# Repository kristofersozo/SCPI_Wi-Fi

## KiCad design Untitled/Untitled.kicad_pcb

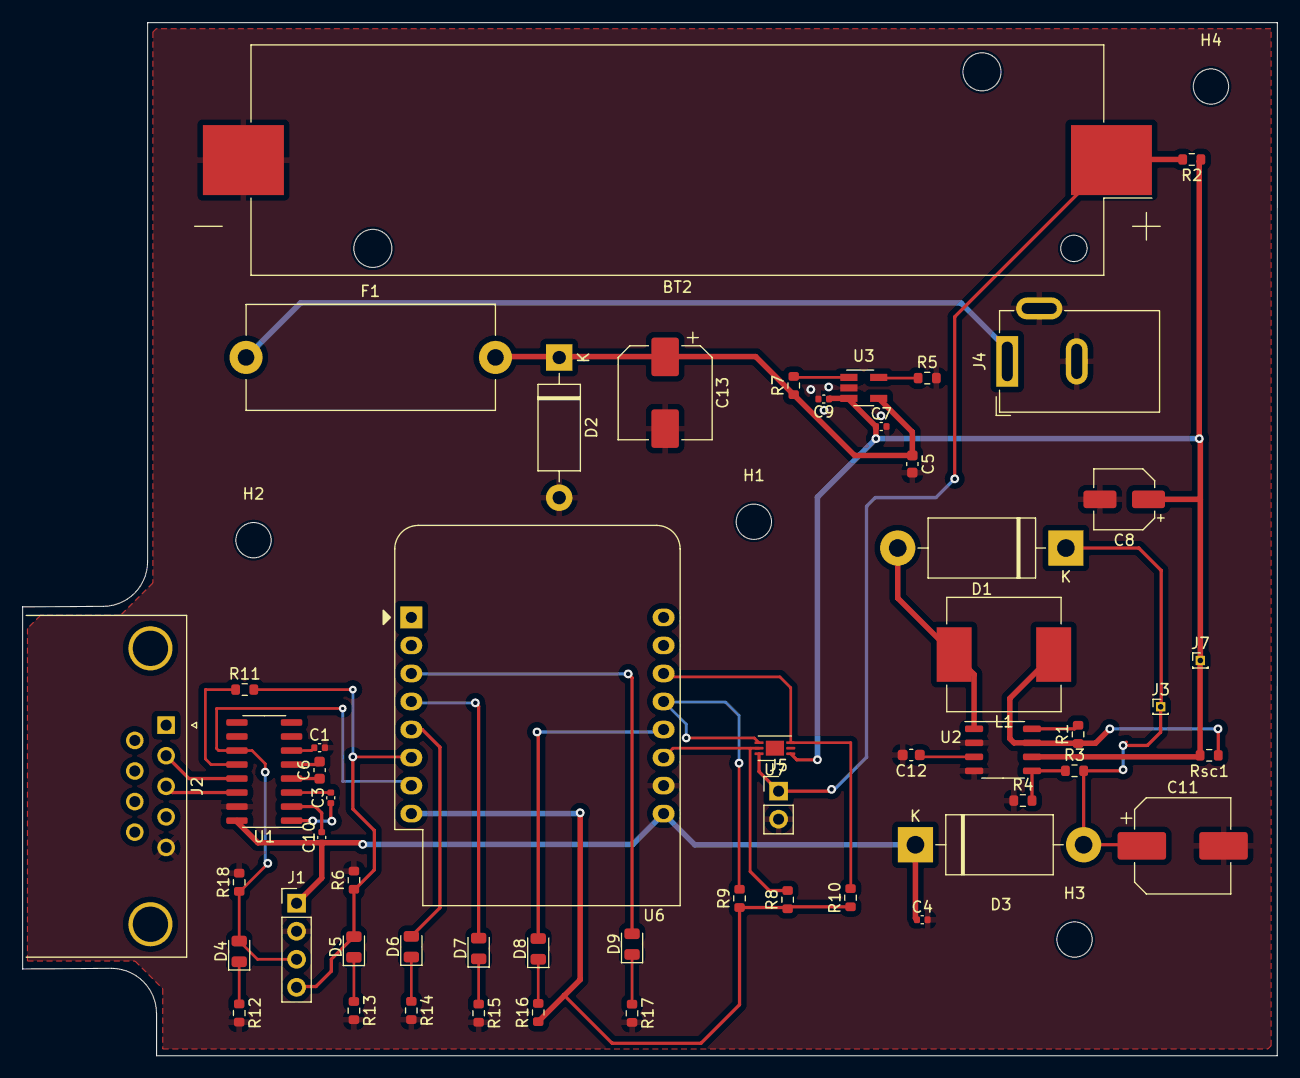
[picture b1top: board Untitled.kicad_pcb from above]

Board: 2 copper layers, 113.7 x 93.6 mm, 58 parts (0 on the bottom side), 39 nets.

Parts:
BT2: Li_ion_Battery_Cell; BatteryHolder_Keystone_1042_1x18650
C1, C3, C4, C7, C9, C10: 100nF; C_0402_1005Metric
C5, C6: 1uF; C_0603_1608Metric
C8: 100uF/16V; CP_Elec_5x5.4
C11: 220uF/16V; CP_Elec_8x10.5
C12: 180pF; C_0603_1608Metric
C13: 4,7uF; CP_Elec_8x10
D1, D3: 1N5822; D_DO-201AD_P15.24mm_Horizontal
D2: SA6.0A; D_DO-15_P12.70mm_Horizontal
D4, D5, D6, D7, D8, D9: LED; LED_0805_2012Metric
F1: 2A; Fuseholder_Cylinder-5x20mm_Stelvio-Kontek_PTF78_Horizontal_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
H1, H2, H3, H4: MountingHole; MountingHole_3.2mm_M3
J1: Conn_01x04_Socket; PinHeader_1x04_P2.54mm_Vertical
J2: DE9_Plug; DSUB-9_Male_Horizontal_P2.77x2.84mm_EdgePinOffset9.90mm_Hou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
J3: 5V5; PinHeader_1x01_P1.00mm_Vertical
J4: Barrel_Jack_Switch_Pin3Ring; BarrelJack_GCT_DCJ200-10-A_Horizontal
J5: Conn_01x02_Pin; PinHeader_1x02_P2.54mm_Vertical
J7: Conn_01x01_Pin; PinHeader_1x01_P1.00mm_Vertical
L1: 7.5uH; L_Vishay_IHLP-4040
R1: 220_1%; R_0603_1608Metric
R2: 100m_1%; R_0603_1608Metric
R3: 47k_1%; R_0603_1608Metric
R4: 15k_1%; R_0603_1608Metric
R5: 1k65_1%; R_0603_1608Metric
R6, R18: 10k_1%; R_0603_1608Metric
R7: 0R_1%; R_0603_1608Metric
R8, R9, R10: 2,2k; R_0603_1608Metric
R11: 5,6K_1%; R_0603_1608Metric
R12, R13, R14, R15, R16, R17: 470_1%; R_0603_1608Metric
Rsc1: 1,18_1%; R_0603_1608Metric
U1: MAX232; SOIC-16_3.9x9.9mm_P1.27mm
U2: MC34063AD; SOP-8_3.9x4.9mm_P1.27mm
U3: LTC4057ES5-4.2_TRMPBF; SOT-23-5_HandSoldering
U6: WeMos_D1_mini; WEMOS_D1_mini_light
U7: LTC2942; DFN-6-1EP_3x2mm_P0.5mm_EP1.65x1.35mm

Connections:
+3.3V: R8.1, R9.1, R10.1, R16.1, U6.8 (3V3)
/5V: C4.1, C10.1, D3.1 (K), J1.1, U1.16 (VCC), U6.9 (5V)
/V_DC_in: C5.1, C13.1, D2.1 (K), F1.2, R7.1, U3.4 (VCC)
/V_bat: C7.1, C8.1, C9.1, J7.1, R2.1, Rsc1.2, U2.6 (Vin), U3.3 (BAT), U7.1 (SENSE+)
GND: BT2.2 (-), C1.2, C4.2, C5.2, C7.2, C8.2, C9.2, C11.2, C12.2, C13.2, D2.2 (A), J1.2, J2.5, J4.2, J4.3, J5.2, R4.1, R5.2, R6.2, R12.2, R13.2, R14.2, R15.2, R17.2, R18.2, U1.15 (GND), U2.2 (SwE), U2.4 (GND), U3.2 (GND), U6.10 (GND), U7.2 (GND)
unnamed: BT2.1 (+), J5.1, R2.2, U7.6 (SENSE-)
unnamed: D1.2 (A), L1.2, U2.1 (SwC)
unnamed: C11.1, D1.1 (K), D3.2 (A), J3.1, R3.2
unnamed: D4.2 (A), J1.3, R18.1, U1.11 (T1IN), U6.7 (CS/D8)
unnamed: D4.1 (K), R12.1
unnamed: D5.2 (A), J1.4, R6.1, R11.2, U6.6 (MOSI/D7)
unnamed: D5.1 (K), R13.1
unnamed: D6.2 (A), U6.5 (MISO/D6)
unnamed: D6.1 (K), R14.1
unnamed: D7.2 (A), U6.4 (SCK/D5)
unnamed: D7.1 (K), R15.1
unnamed: D8.2 (A), U6.12 (D3)
unnamed: D8.1 (K), R16.2
unnamed: D9.2 (A), U6.3 (D0)
unnamed: D9.1 (K), R17.1
unnamed: F1.1, J4.1
unnamed: C3.1, U1.1 (C1+)
unnamed: C3.2, U1.3 (C1-)
unnamed: C6.1, U1.4 (C2+)
unnamed: C6.2, U1.5 (C2-)
unnamed: J2.2, U1.13 (R1IN)
unnamed: R11.1, U1.12 (R1OUT)
unnamed: J2.3, U1.14 (T1OUT)
unnamed: C10.2, U1.2 (VS+)
unnamed: C1.1, U1.6 (VS-)
unnamed: R1.2, U2.8 (DC)
unnamed: L1.1, R1.1, Rsc1.1, U2.7 (Ipk)
unnamed: C12.1, U2.3 (TC)
unnamed: R3.1, R4.2, U2.5 (Vfb)
unnamed: R7.2, U3.1 (ON/OFF)
unnamed: R5.1, U3.5 (PROG)
unnamed: R8.2, U6.11 (D4), U7.5 (~AL/CC)
unnamed: R10.2, U6.14 (SCL/D1), U7.3 (SCL)
unnamed: R9.2, U6.13 (SDA/D2), U7.4 (SDA)

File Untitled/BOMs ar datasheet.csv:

"Source:","/Users/kristofersozolins/Downloads/Universitāte/3. kurss/Akademiska_prakse2/db9_female_max232/Untitled/Untitled.kicad_sch"
"Date:","Friday, 03 November 2023 at 11:30:09"
"Tool:","Eeschema (7.0.0-0)"
"Generator:","/Applications/KiCad/KiCad.app/Contents/SharedSupport/plugins/bom_csv_grouped_by_value.py"
"Component Count:","58"

"Collated Components:"

"Item","Qty","Reference(s)","Value","LibPart","Footprint","Datasheet","DNP","Availability","Check_prices","Description","MF","MP","Manufacturer","Package","Price","Purchase-URL","Sim.Device","Sim.Pins","SnapEDA_Link"
"1","1","BT2","Li_ion_Battery_Cell","Device:Battery_Cell","Battery:BatteryHolder_Keystone_1042_1x18650","~","","","","","","","","","","","","","",""
"2","6","C1, C3, C4, C7, C9, C10","100nF","Device:C_Small","Capacitor_SMD:C_0402_1005Metric","C338011","","","","","","","","","","","","","",""
"3","2","C5, C6","1uF","Device:C_Small","Capacitor_SMD:C_0603_1608Metric","C76617","","","","","","","","","","","","","",""
"4","1","C8","100uF/16V","Device:C_Polarized_Small_US","Capacitor_SMD:CP_Elec_5x5.4","C4747962","","","","","","","","","","","","","",""
"5","1","C11","220uF/16V","Device:C_Small","Capacitor_SMD:CP_Elec_8x10.5","C242038","","","","","","","","","","","","","",""
"6","1","C12","180pF","Device:C_Small","Capacitor_SMD:C_0603_1608Metric","C565593","","","","","","","","","","","","","",""
"7","1","C13","4u7","Device:C_Polarized_Small_US","Capacitor_SMD:CP_Elec_8x10","C487544","","","","","","","","","","","","","",""
"8","2","D1, D3","1N5822","Diode:1N5822","Diode_THT:D_DO-201AD_P15.24mm_Horizontal","C908721","","","","","","","","","","","","","",""
"9","1","D2","SA6.0A","Diode:1N5400","Diode_THT:D_DO-15_P12.70mm_Horizontal","C523137","","","","","","","","","","","","D","1=K 2=A",""
"10","6","D4, D5, D6, D7, D8, D9","LED","Device:LED","LED_SMD:LED_0805_2012Metric","C86865","","","","","","","","","","","","","",""
"11","1","F1","2A","Device:Polyfuse_Small","Fuse:Fuseholder_Cylinder-5x20mm_Stelvio-Kontek_PTF78_Horizontal_Open","C2997155","","","","","","","","","","","","","",""
"12","4","H1, H2, H3, H4","MountingHole","Mechanical:MountingHole","MountingHole:MountingHole_3.2mm_M3","~","","","","","","","","","","","","","",""
"13","1","J1","Conn_01x04_Socket","Connector:Conn_01x04_Socket","Connector_PinHeader_2.54mm:PinHeader_1x04_P2.54mm_Vertical","~","","","","","","","","","","","","","",""
"14","1","J2","DE9_Plug","Connector:DE9_Plug","Connector_Dsub:DSUB-9_Male_Horizontal_P2.77x2.84mm_EdgePinOffset9.90mm_Housed_MountingHolesOffset11.32mm"," ~","","","","","","","","","","","","","",""
"15","1","J3","5V5","Connector:Conn_01x01_Socket","Connector_PinHeader_2.54mm:PinHeader_1x01_P2.54mm_Vertical","C429850","","","","","","","","","","","","","",""
"16","1","J4","Barrel_Jack_Switch_Pin3Ring","Connector:Barrel_Jack_Switch_Pin3Ring","Connector_BarrelJack:BarrelJack_GCT_DCJ200-10-A_Horizontal","~","","","","","","","","","","","","","",""
"17","1","J5","Conn_01x02_Pin","Connector:Conn_01x02_Pin","Connector_PinHeader_2.54mm:PinHeader_1x02_P2.54mm_Vertical","C5224022","","","","","","","","","","","","","",""
"18","1","J7","Conn_01x01_Pin","Connector:Conn_01x01_Pin","Connector_PinHeader_2.54mm:PinHeader_1x01_P2.54mm_Vertical","C429850","","","","","","","","","","","","","",""
"19","1","L1","7.5uH","Device:L","Inductor_SMD:L_Vishay_IHLP-4040","C918982","","","","","","","","","","","","","",""
"20","1","R1","220_1%","Device:R_Small","Resistor_SMD:R_0603_1608Metric","C177304","","","","","","","","","","","","","",""
"21","1","R2","100m_1%","Device:R_Small","Resistor_SMD:R_0603_1608Metric","C175644","","","","","","","","","","","","","",""
"22","1","R3","47k_1%","Device:R_Small","Resistor_SMD:R_0603_1608Metric","C25819","","","","","","","","","","","","","",""
"23","1","R4","15k_1%","Device:R_Small","Resistor_SMD:R_0603_1608Metric","C22809","","","","","","","","","","","","","",""
"24","1","R5","1k65_1%","Device:R_Small","Resistor_SMD:R_0603_1608Metric","C185357","","","","","","","","","","","","","",""
"25","1","R6","10k_1%","Device:R_Small","Resistor_SMD:R_0603_1608Metric","C25804","","","","","","","","","","","","","",""
"26","1","R7","0R_1%","Device:R_Small","Resistor_SMD:R_0603_1608Metric","C115304","","","","","","","","","","","","","",""
"27","3","R8, R9, R10","2k2","Device:R_Small","Resistor_SMD:R_0603_1608Metric","C5140136","","","","","","","","","","","","","",""
"28","1","R11","5k6_1%","Device:R_Small","Resistor_SMD:R_0603_1608Metric","C177628","","","","","","","","","","","","","",""
"29","6","R12, R13, R14, R15, R16, R17","470_1%","Device:R_Small","Resistor_SMD:R_0603_1608Metric","C497138","","","","","","","","","","","","","",""
"30","1","R18","10k_1%","Device:R_Small","Resistor_SMD:R_0805_2012Metric","C25804","","","","","","","","","","","","","",""
"31","1","R19","1R18_1%","Device:R_Small","Resistor_SMD:R_0603_1608Metric","C482619","","","","","","","","","","","","","",""
"32","1","U1","MAX232","Interface_UART:MAX232","Package_SO:SOIC-16_3.9x9.9mm_P1.27mm","C45119","","","","","","","","","","","","","",""
"33","1","U2","MC34063AD","Regulator_Switching:MC34063AD","Package_SO:SOP-8_3.9x4.9mm_P1.27mm","C3014308","","","","","","","","","","","","","",""
"34","1","U3","LTC4057ES5-4.2_TRMPBF","LTC4057ES5-4.2_TRMPBF:LTC4057ES5-4.2_TRMPBF","Package_TO_SOT_SMD:SOT-23-5_HandSoldering","","","","In Stock","https://www.snapeda.com/parts/LTC4057ES5-4.2%23TRMPBF/Analog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","Linear Li-Ion Battery Charger with Thermal Regulation in ThinSOT","Analog Devices","LTC4057ES5-4.2#TRMPBF","Analog Devices","SOT-5 Analog Devices","None","https://www.snapeda.com/api/url_track_click_mouser/?unipart_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 Devices&part_name=LTC4057ES5-4.2#TRMPBF&search_term=None","","","https://www.snapeda.com/parts/LTC4057ES5-4.2%23TRMPBF/Analog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"
"35","1","U6","WeMos_D1_mini","MCU_Module:WeMos_D1_mini","Module:WEMOS_D1_mini_light","https://wiki.wemos.cc/products:d1:d1_mini#documentation","","","","","","","","","","","","","",""
"36","1","U7","LTC2942","Battery_Management:LTC2942","Package_DFN_QFN:DFN-6-1EP_3x2mm_P0.5mm_EP1.65x1.35mm","C683656","","","","","","","","","","","","","",""
